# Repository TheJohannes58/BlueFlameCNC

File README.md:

All the Voron build related info and sources I can find and brought into one place for convenance.

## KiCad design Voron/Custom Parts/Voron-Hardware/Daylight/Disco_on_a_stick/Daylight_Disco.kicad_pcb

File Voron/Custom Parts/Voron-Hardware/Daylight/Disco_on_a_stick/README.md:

# Disco on a stick

18 Addressable RGB leds to for a party in your Voron.

## BOM
| Quantity | Value                          | Package |
|----------|--------------------------------|---------|
|       15 | 100nF Capacitor                | 0805    |
|       18 | Addressable RGB LED (WS2812B)  | 5050    |
|        2 | JST-XH (2.54) angled connector | 3pin    |

## Changelog

### V1.1
Added second JST-XH connector to chain to the next Disco on a Stick.  
Thanks to DarkNeutrino for the contribution.

### V1.0
Initial public release.

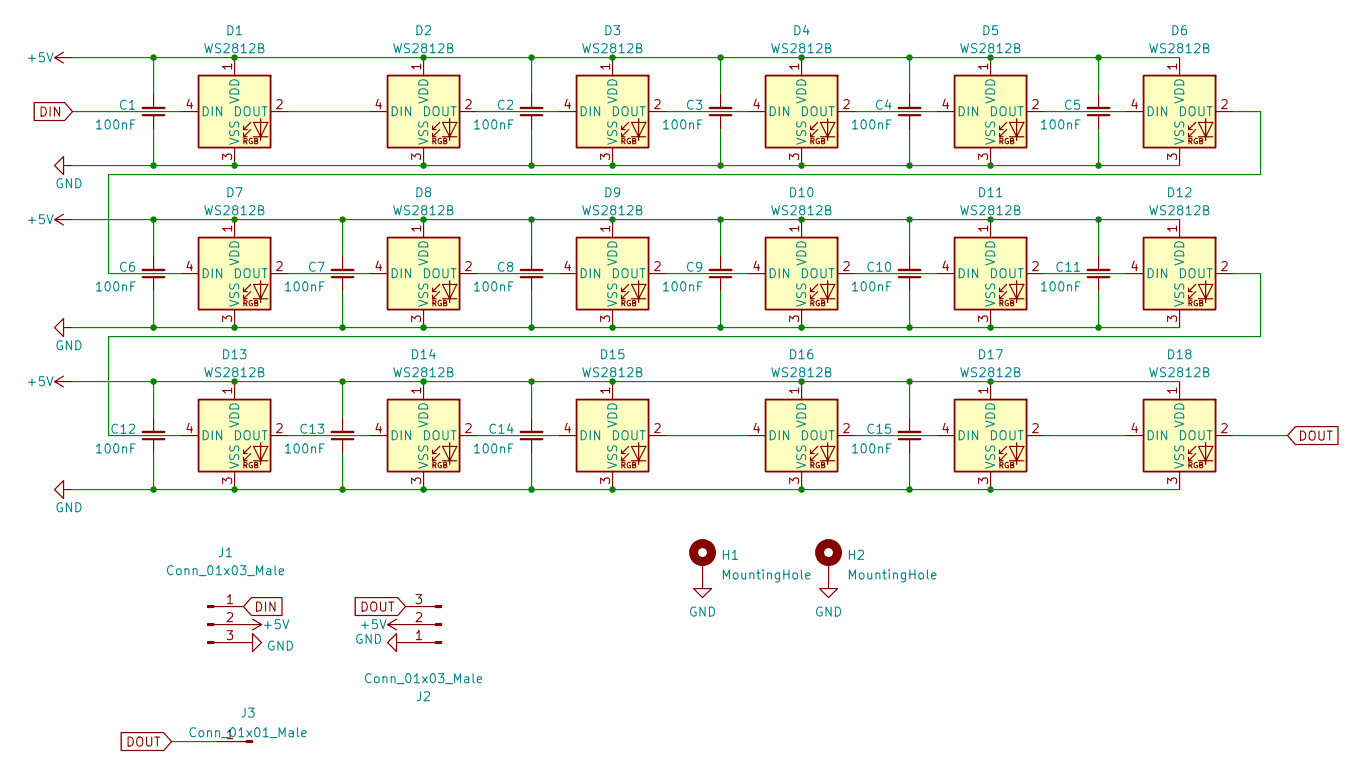
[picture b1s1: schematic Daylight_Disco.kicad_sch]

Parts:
C1, C2, C3, C4, C5, C6, C7, C8, C9, C10, C11, C12, C13, C14, C15: 100nF; C_0805_2012Metric_Pad1.18x1.45mm_HandSolder
D1, D2, D3, D4, D5, D6, D7, D8, D9, D10, D11, D12, D13, D14, D15, D16, D17, D18: WS2812B; LED_WS2812B_PLCC4_5.0x5.0mm_P3.2mm
H1, H2: MountingHole; MountingHole_3.2mm_M3_Pad_Via
J1, J2: Conn_01x03_Male; JST_XH_S3B-XH-A-1_1x03_P2.50mm_Horizontal
J3: Conn_01x01_Male; PinHeader-1-with-SMDpad

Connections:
+5V: C1.2, C2.2, C3.2, C4.2, C5.2, C6.2, C7.2, C8.2, C9.2, C10.2, C11.2, C12.2, C13.2, C14.2, C15.2, D1.1 (VDD), D2.1 (VDD), D3.1 (VDD), D4.1 (VDD), D5.1 (VDD), D6.1 (VDD), D7.1 (VDD), D8.1 (VDD), D9.1 (VDD), D10.1 (VDD), D11.1 (VDD), D12.1 (VDD), D13.1 (VDD), D14.1 (VDD), D15.1 (VDD), D16.1 (VDD), D17.1 (VDD), D18.1 (VDD), J1.2, J2.2
DIN: D1.4 (DIN), J1.1
DOUT: D18.2 (DOUT), J2.3, J3.1
GND: C1.1, C2.1, C3.1, C4.1, C5.1, C6.1, C7.1, C8.1, C9.1, C10.1, C11.1, C12.1, C13.1, C14.1, C15.1, D1.3 (VSS), D2.3 (VSS), D3.3 (VSS), D4.3 (VSS), D5.3 (VSS), D6.3 (VSS), D7.3 (VSS), D8.3 (VSS), D9.3 (VSS), D10.3 (VSS), D11.3 (VSS), D12.3 (VSS), D13.3 (VSS), D14.3 (VSS), D15.3 (VSS), D16.3 (VSS), D17.3 (VSS), D18.3 (VSS), H1.1, H2.1, J1.3, J2.1
unnamed: D1.2 (DOUT), D2.4 (DIN)
unnamed: D2.2 (DOUT), D3.4 (DIN)
unnamed: D3.2 (DOUT), D4.4 (DIN)
unnamed: D4.2 (DOUT), D5.4 (DIN)
unnamed: D5.2 (DOUT), D6.4 (DIN)
unnamed: D6.2 (DOUT), D7.4 (DIN)
unnamed: D7.2 (DOUT), D8.4 (DIN)
unnamed: D8.2 (DOUT), D9.4 (DIN)
unnamed: D10.2 (DOUT), D11.4 (DIN)
unnamed: D9.2 (DOUT), D10.4 (DIN)
unnamed: D11.2 (DOUT), D12.4 (DIN)
unnamed: D12.2 (DOUT), D13.4 (DIN)
unnamed: D13.2 (DOUT), D14.4 (DIN)
unnamed: D14.2 (DOUT), D15.4 (DIN)
unnamed: D15.2 (DOUT), D16.4 (DIN)
unnamed: D16.2 (DOUT), D17.4 (DIN)
unnamed: D17.2 (DOUT), D18.4 (DIN)

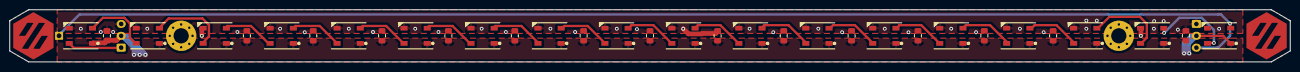
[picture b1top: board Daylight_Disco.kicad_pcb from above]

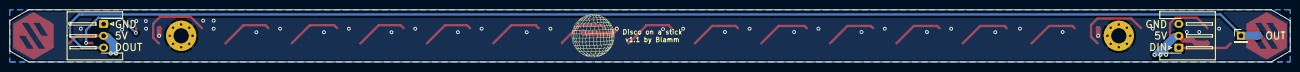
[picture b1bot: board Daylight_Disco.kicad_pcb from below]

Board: 2 copper layers, 270.0 x 11.0 mm, 38 parts (3 on the bottom side), 21 nets.

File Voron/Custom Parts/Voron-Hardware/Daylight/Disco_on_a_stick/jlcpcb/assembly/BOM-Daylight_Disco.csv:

Comment,Designator,Footprint,LCSC
WS2812B,"D1,D10,D11,D12,D13,D14,D15,D16,D17,D18,D2,D3,D4,D5,D6,D7,D8,D9",LED_WS2812B_PLCC4_5.0x5.0mm_P3.2mm,C2761795
100nF,"C1,C10,C11,C12,C13,C14,C15,C2,C3,C4,C5,C6,C7,C8,C9",C_0805_2012Metric_Pad1.18x1.45mm_HandSolder,C28233
Conn_01x01_Male,J3,PinHeader-1-with-SMDpad,
Conn_01x03_Male,J2,JST_XH_S3B-XH-A-1_1x03_P2.50mm_Horizontal,
Conn_01x03_Male,J1,JST_XH_S3B-XH-A-1_1x03_P2.50mm_Horizontal,

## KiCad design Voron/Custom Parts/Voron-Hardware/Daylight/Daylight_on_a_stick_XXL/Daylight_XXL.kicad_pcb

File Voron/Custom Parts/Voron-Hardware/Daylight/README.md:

# Daylight on a stick

The original Daylight on a Stick is a chainable 24V LED bar, to be used with high quality 4000K LEDs to give the illusion of daylight in your Voron. Great when making photo's of your prints, or want to see the colors how they will look in the outside world.  

Ideally popuplated with 90+ CRI LEDs (3V, ~60mA), but currently LCSC does not carry those, so the BOM has 80 CRI ones. Just as bright, bit less accurate color reproduction. Would advice to use the proper ones for the intended experience.  
So if you solder them yourself, get better leds, for example:  
[Digikey CRI90+](https://www.digikey.com/en/products/detail/JB2835AWT-W-U40GA0000-N0000001/2138-JB2835AWT-W-U40GA0000-N0000001CT-ND/10820479)  
[AliExpress CRI95+](https://www.aliexpress.com/item/4000389792048.html) (non affiliate link)

Use any angled 2.54mm(0.1") connector such as a 90 degree pinheader, angled JST-XH or Molex KK254.

The RGB versions use any 4 pin 5050 package addressable led, like the known WS2812B, the SK6812 (with or without white) etcetera. Also 100nF capacitors in 0805 package are added to decouple the leds.

## Varieties

- [Daylight on a Stick](./Daylight_on_a_stick/) (for Voron sizes of 250mm and upwards)
- [Daylight on a Matchstick](./Daylight_on_a_matchstick/) (for V0.1 or other printers for ants)
- [Daylight on a Stick XXL](./Daylight_on_a_stick_XXL/) (for 350 or bigger printers)
- [Disco on a Stick](./Disco_on_a_stick/) (RGB addressable LEDs for the big printers)
- [Rainbow on a Matchstick](./Rainbow_on_a_matchstick/) (RGB addressable LEDS for the small printers)
- [Disco on a Stick XXL](./Disco_on_a_stick_XXL/) (RGB addressable LEDs for for 350 or bigger printers)

## Klipper
Use the regular Daylight on a Stick/Matchstick directly on 24V or hook them up to a spare heater output on your controlboard. In this last case you can control it using:

```
[output_pin daylight]
pin: ##PIN##
pwm: True
cycle_time: 0.01
```

For the RGB ones, put them on the RGB output of your controlboard and configure them according to the [Klipper config reference](https://www.klipper3d.org/Config_Reference.html#neopixel). `chain_length` is 18 for the big stick, 10 for the matchstick.

## Mounting

The [bracket for 2020 profiles](./STL/Brackets_2020.stl) are mounted to the profile using an M3x6 or M3x8 SHCS together with a roll-in nut, and take an M3 heat insert to mount the strip onto the bracket itself.  

On 1515 frames like the V0.1 the [brackets for 1515 profiles](./STL/Brackets_1515_x2.stl) are used. They take an M3 heat insert and clip into the extrusion. Mount the pcb on them with an M3x6 BHCS screw.
The clip geometry used in these was developed by [Zruncho for their ZeroPanels](https://github.com/zruncho3d/ZeroPanels).

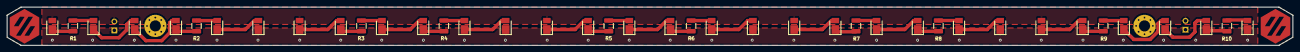
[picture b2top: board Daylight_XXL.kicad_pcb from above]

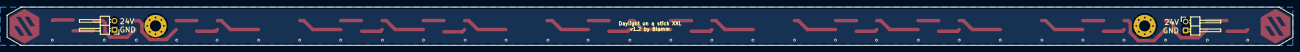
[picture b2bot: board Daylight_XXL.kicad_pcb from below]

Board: 2 copper layers, 370.0 x 11.0 mm, 44 parts (2 on the bottom side), 37 nets.

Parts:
D1, D2, D3, D4, D5, D6, D7, D8, D9, D10, D11, D12, D13, D14, D15, D16, D17, D18, D19, D20, D21, D22, D23, D24, D25, D26, D27, D28, D29, D30: LED_ALT; LED_PLCC_2835_Handsoldering
H1, H2: MountingHole; MountingHole_3.2mm_M3_Pad_Via
J1: Conn_01x02_Female; PinHeader_1x02_P2.54mm_Horizontal_mirrored
J2: Conn_01x02_Female; PinHeader_1x02_P2.54mm_Horizontal
R1, R2, R3, R4, R5, R6, R7, R8, R9, R10: 100R 0.5W; R_1210_3225Metric_Pad1.30x2.65mm_HandSolder

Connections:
+24V: D1.2 (A), D7.2 (A), D13.2 (A), D19.2 (A), D25.2 (A), J1.2, J2.2
GND: D6.1 (K), D12.1 (K), D18.1 (K), D24.1 (K), D30.1 (K), H1.1, H2.1, J1.1, J2.1
unnamed: D1.1 (K), R1.2
unnamed: D2.1 (K), D3.2 (A)
unnamed: D4.1 (K), R2.2
unnamed: D3.1 (K), D4.2 (A)
unnamed: D5.1 (K), D6.2 (A)
unnamed: D5.2 (A), R2.1
unnamed: D7.1 (K), D8.2 (A)
unnamed: D8.1 (K), R3.2
unnamed: D9.2 (A), R3.1
unnamed: D10.1 (K), R4.2
unnamed: D9.1 (K), D10.2 (A)
unnamed: D11.1 (K), D12.2 (A)
unnamed: D11.2 (A), R4.1
unnamed: D13.1 (K), D14.2 (A)
unnamed: D14.1 (K), R5.2
unnamed: D15.1 (K), D16.2 (A)
unnamed: D15.2 (A), R5.1
unnamed: D16.1 (K), R6.2
unnamed: D17.1 (K), D18.2 (A)
unnamed: D19.1 (K), D20.2 (A)
unnamed: D20.1 (K), R7.2
unnamed: D21.1 (K), D22.2 (A)
unnamed: D21.2 (A), R7.1
unnamed: D22.1 (K), R8.2
unnamed: D23.1 (K), D24.2 (A)
unnamed: D23.2 (A), R8.1
unnamed: D25.1 (K), D26.2 (A)
unnamed: D26.1 (K), R9.2
unnamed: D27.1 (K), D28.2 (A)
unnamed: D27.2 (A), R9.1
unnamed: D28.1 (K), D29.2 (A)
unnamed: D29.1 (K), R10.2
unnamed: D30.2 (A), R10.1
unnamed: D2.2 (A), R1.1
unnamed: D17.2 (A), R6.1

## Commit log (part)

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2023-12-23 new file: CAD/Voron_2.4r2_Assembly_STEP.zip new file: Drawing_DXFs/Build_Plate/MIC6_Bed_V2_250.step new file: Drawing_DXFs/Build_Plate/MIC6_Bed_V2_300.step new file: Drawing_DXFs/Build_Plate/MIC6_Bed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
2023-12-23 new file: Voron/Voron-Switchwire/.gitignore new file: Voron/Voron-Switchwire/CAD/Pinion.f3d new file: Voron/Voron-Switchwire/CAD/Pinion.step new file: Voron/Voron-Switchwire/CAD/Switchwire_Assembly_v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
2023-12-23 new file: Voron/Voron-Extras/Klipper_NP++_Language.xml new file: Voron/Voron-Hardware/Afterburner_Toolhead_PCB/CAD/Afterburner-ERCF-PCB.step new file: Voron/Voron-Hardware/Afterburner_Toolhead_PCB/CA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
2023-12-23 new file: Voron/Voron-Parts-DIN/DIN_Mounts/Controllers/Bigtreetech/GTR_2pc.stl new file: Voron/Voron-Parts-DIN/DIN_Mounts/Controllers/Bigtreetech/MOT_EXP.stl new file: Voron/Voron-Parts-DIN/DIN_Mount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
2023-12-23 new file: Voron/Voron-0.2r1/CAD/ADXL_Mounts/MiniSB_adxl_mount_adafruit_19mm_c_c.step new file: Voron/Voron-0.2r1/CAD/ADXL_Mounts/MiniSB_adxl_mount_adafruit_LIS3DH.step new file: Voron/Voron-0.2r1/CAD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
2023-12-23 new file: BIGTREETECH/BIGTREETECH-OCTOPUS-V1.0/3D/BIGTREETECH Octopus V1.0.stp new file: BIGTREETECH/BIGTREETECH-OCTOPUS-V1.0/BIGTREETECH_Octopus_EN_updated_0719.pdf new file: BIGTREETECH/BIGTREETECH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
2023-12-23 new file: PicoPendant/.gitignore new file: PicoPendant/CircuitBoard/PCB_PicoCtl_Pcb_2023-02-23.json new file: PicoPendant/CircuitBoard/README.md new file: PicoPendant/CircuitBoard/SCH_PicoController_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
2023-12-24 new file: OrcaSlicer/.clang-format new file: OrcaSlicer/.dockerignore new file: OrcaSlicer/.doxygen new file: OrcaSlicer/.github/FUNDING.yml new file: OrcaSlicer/.github/ISSUE_TEMPLATE/bug_report.yml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
2023-12-24 new file: bearings/Raindew-F695-RS.png deleted: bearings/Raindew-F695-RS.webp
2023-12-26 new file: bearings/F695-2RS/README.md modified: bearings/images/F695-2RS.png
2023-12-26 new file: bearings/Bearings.md deleted: bearings/F695-2RS.md renamed: bearings/CAD/F695 Bearing.step -> bearings/F695-2RS/CAD/F695 Bearing.step renamed: bearings/CAD/F695-ltk.step -> bearings/F695-2R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
2023-12-26 modified: bearings/625-2RS/images/625-2RS.png new file: bearings/625-2RS/images/ball-bearing-625-2rs.jpg modified: bearings/F695-2RS/images/F695-2RS.png
2023-12-26 new file: bearings/Bearings.md
2023-12-26 deleted: Bearings/Bearings.md renamed: Bearings/625-2RS/README.md -> Build Resources/Bearings/625-2RS/README.md renamed: Bearings/625-2RS/images/625-2RS.png -> Build Resources/Bearings/625-2RS/images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
2023-12-26 modified: Build Resources/Readme.md
2023-12-27 deleted: BIGTREETECH/BIGTREETECH-OCTOPUS-V1.0/3D/BIGTREETECH Octopus V1.0.stp deleted: BIGTREETECH/BIGTREETECH-OCTOPUS-V1.0/BIQU Octopus wiring diagram-V1.0-2021-7-9.png deleted: BIGTREETECH/BIGTREET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
2023-12-27 deleted: BIGTREETECH/BIGTREETECH-OCTOPUS-V1.0/Firmware/DFU Update bootloader/Octopus-DFU Update bootloader - en.pdf deleted: BIGTREETECH/BIGTREETECH-OCTOPUS-V1.0/Firmware/DFU Update bootloader/bootlo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
2023-12-27 new file: Build Resources/Electronics/BIGTREETECH/BIGTREETECH-OCTOPUS-V1.0/BIQU Octopus wiring diagram-V1.0-2021-7-9.png
2023-12-27 new file: Build Resources/Electronics/BIGTREETECH/BIGTREETECH-OCTOPUS-V1.0/Firmware/Marlin-bugfix-2.0.9.3.x/README.md new file: Build Resources/Electronics/BIGTREETECH/BIGTREETECH-OCTOPUS-V1.0/Firmwa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
2023-12-27 new file: Build Resources/Electronics/BIGTREETECH/BIGTREETECH-OCTOPUS-V1.0/BIQU Octopus wiring diagram-V1.0-2021-7-9.png new file: Build Resources/Electronics/BIGTREETECH/BIGTREETECH-OCTOPUS-V1.0/REA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
2023-12-27 new file: Build Resources/Electronics/BIGTREETECH/BIGTREETECH-OCTOPUS-V1.0/Hardware/BIGTREETECH Octopus - PIN.pdf new file: Build Resources/Electronics/BIGTREETECH/BIGTREETECH-OCTOPUS-V1.0/Hardware/B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
2023-12-27 new file: Build Resources/Electronics/BIGTREETECH/BIGTREETECH-OCTOPUS-V1.0/Firmware/DFU Update bootloader/Octopus-DFU Update bootloader - en.pdf new file: Build Resources/Electronics/BIGTREETECH/BIGT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
2023-12-27 new file: temp/RepRapFirmware/F446-OctoPus/README.md new file: temp/RepRapFirmware/F446-OctoPus/filaments/nop.g new file: temp/RepRapFirmware/F446-OctoPus/firmware.bin new file: temp/RepRapFirmware/F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
2023-12-27 renamed: Build Resources/temp/Marlin-bugfix-2.0.9.3.x/.editorconfig -> Build Resources/Electronics/temp/Marlin-bugfix-2.0.9.3.x/.editorconfig renamed: Build Resources/temp/Marlin-bugfix-2.0.9.3.x/.gi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
2023-12-27 renamed: Build Resources/Electronics/BIGTREETECH/temp/RepRapFirmware/F446-OctoPus/README.md -> Build Resources/Electronics/BIGTREETECH/BIGTREETECH-OCTOPUS-V1.0/Firmware/RepRapFirmware/F446-OctoPus/RE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
2023-12-27 renamed: Build Resources/Electronics/BIGTREETECH/temp/RepRapFirmware/RRFBuild-SourceCode/.vscode/.cortex-debug.peripherals.state.json -> Build Resources/Electronics/BIGTREETECH/BIGTREETECH-OCTOPUS-V1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
2023-12-27 renamed: Build Resources/Electronics/BIGTREETECH/temp/RepRapFirmware/RRFBuild-SourceCode/DuetWiFiSocketServer/.cproject -> Build Resources/Electronics/BIGTREETECH/BIGTREETECH-OCTOPUS-V1.0/Firmware/Re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
2023-12-27 renamed: Build Resources/Electronics/BIGTREETECH/temp/RepRapFirmware/RRFBuild-SourceCode/CoreN2G/src/AnalogIn.h -> Build Resources/Electronics/BIGTREETECH/BIGTREETECH-OCTOPUS-V1.0/Firmware/RepRapFirm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
2023-12-27 renamed: Build Resources/Electronics/BIGTREETECH/BIGTREETECH-OCTOPUS-V1.0/3D/BIGTREETECH Octopus V1.0.stp -> BIGTREETECH/BIGTREETECH-OCTOPUS-V1.0-master/3D/BIGTREETECH Octopus V1.0.stp renamed: Build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
2023-12-27 deleted: "BIGTREETECH/BIGTREETECH-OCTOPUS-V1.0-master/Firmware/DFU Update bootloader/Octopus-DFU\346\233\264\346\226\260\345\274\225\345\257\274\347\250\213\345\272\217-\344\270\255\346\226\207.pdf"
2023-12-27 modified: .vscode/settings.json modified: Build Resources/Listings/Buylist.md
2023-12-29 new file: Build Resources/Frames/Fermio/Readme.md new file: Build Resources/Frames/Misumi/2019_US_2724.pdf new file: Build Resources/Frames/Misumi/HFSB6-3060-520-AH105-BH415-AV180.pdf new file: Build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
2023-12-29 modified: Build Resources/Frames/Readme.md new file: Build Resources/Frames/images/misumi alu prof.png
2023-12-29 Rename misumi alu prof.png to misumi_alu-prof.png
2023-12-29 new file: Build Resources/Frames/Misumi/Readme.md new file: Build Resources/Frames/images/30x60-Aluminum-Extrusion-6_Series_Base_30.png
2023-12-29 new file: Build Resources/Fasteners/Voron Switchwire/Readme.md new file: Build Resources/Fasteners/images/VRN-SW-HRDWR-KIT.jpg
2023-12-29 modified: Build Resources/Fasteners/Voron Switchwire/Readme.md new file: Build Resources/Fasteners/images/VRN-SW-TNUTS.png
2023-12-30 modified: Build Resources/Fasteners/Voron 2.4/Readme.md new file: Build Resources/Fasteners/images/MCH-NT-HH-M3-50.jpg new file: Build Resources/Fasteners/images/VRN-V24-TNUTS.jpg
2023-12-30 modified: Build Resources/Fasteners/Voron Switchwire/Lecktor.com.md
2023-12-30 new file: Build Resources/Frames/next.csv
2023-12-30 modified: Build Resources/Frames/next.csv deleted: Build Resources/Frames/next.csv
2023-12-30 modified: Build Resources/Frames/template.csv deleted: Build Resources/Listings/BuylistTemplate.md renamed: Build Resources/Bearings/625-2RS/README.md -> Build Resources/Motion/Bearings/625-2RS/READM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
2023-12-30 modified: Build Resources/Buildplate/readme.md new file: Build Resources/Electronics/Stepper Motors/Readme.md new file: Build Resources/Electronics/images/17HS15-1504S1.jpg new file: Build Resources/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
2023-12-30 modified: Build Resources/Electronics/Stepper Motors/17HS15-1504S1 stepper.md modified: Build Resources/Electronics/Stepper Motors/17HS15-1504S1 stepper.md
2023-12-30 modified: Build Resources/Electronics/Power Supply/LRS-350-24.md
2023-12-30 new file: Build Resources/Electronics/Stepper Motors/17HS08-1004S-H.md new file: Build Resources/Electronics/images/17HS08-1004S-H.jpg new file: Build Resources/Electronics/images/17HS08-1004S-H.webp
2023-12-30 modified: Build Resources/Electronics/Stepper Motors/Readme.md renamed: Build Resources/Electronics/images/17HS15-1504S1 - Copy.webp -> Build Resources/Electronics/images/17HS15-1504S1 - shift.webp
2023-12-30 new file: Build Resources/Electronics/Stepper Motors/PDF/17HS08-1004S-H.pdf new file: Build Resources/Electronics/Stepper Motors/PDF/17HS15-1504S1.pdf new file: Build Resources/Electronics/Stepper Mo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
2023-12-30 modified: Build Resources/Electronics/Power Supply/LRS-350-24.md new file: Build Resources/Electronics/Power Supply/PDF/LRS-350-24.pdf new file: Build Resources/Electronics/Power Supply/PDF/RS-25.pdf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
2023-12-31 modified: Build Resources/Electronics/Readme.md modified: Build Resources/Fasteners/Readme.md
2023-12-31 modified: Build Resources/Fasteners/Readme.md deleted: Build Resources/Fasteners/images/MCH-NT-HH-M3-50.jpg deleted: Build Resources/Fasteners/images/VRN-24-HRDWR-KIT-BLK.jpg new file: Build Resource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
2023-12-31 new file: Build Resources/Fasteners/Voron Switchwire/Bolt-Depot.md new file: Build Resources/Fasteners/Voron Switchwire/McMaster.md
2023-12-31 modified: Build Resources/Fasteners/Voron Switchwire/Switchwire.csv new file: Build Resources/Fasteners/Voron Switchwire/Switchwire.xlsx
2024-01-01 new file: Build Resources/Electronics/Power Supply/LRS-150-24.md new file: Build Resources/Electronics/Power Supply/PDF/LRS-150.PDF new file: Build Resources/Electronics/images/LRS-150-24.webp
2024-01-01 Rename LRS-150.PDF to LRS-150.pdf
2024-01-01 modified: Build Resources/Electronics/Power Supply/LRS-150-24.md modified: Build Resources/Electronics/Power Supply/LRS-350-24.md modified: Build Resources/Electronics/Power Supply/RS-25-5.md
2024-01-01 deleted: Build Resources/Electronics/Power Supply/CAD/LRS-150-24.stl deleted: Build Resources/Electronics/Power Supply/CAD/LRS-350-24.stl deleted: Build Resources/Electronics/Power Supply/CAD/RS-25-5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
2024-01-01 new file: Build Resources/Electronics/Fans/CAD/414FH.stp new file: Build Resources/Electronics/Fans/readme.md new file: Build Resources/Electronics/images/FYSETC.webp new file: Build Resources/Electr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
2024-01-01 modified: Build Resources/Electronics/images/FYSETC.webp
2024-01-01 new file: Build Resources/Electronics/Wiring/readme.md
2024-01-02 modified: Build Resources/Electronics/Fans/readme.md modified: Build Resources/Electronics/Wiring/readme.md deleted: Build Resources/Electronics/images/FYSETC.webp new file: Build Resources/Electroni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
2024-01-02 modified: Build Resources/Electronics/images/43030-0007.webp modified: Build Resources/Electronics/images/43031-0007.webp modified: Build Resources/Electronics/images/43640-0201.webp modified: Build 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
2024-01-02 modified: Build Resources/Electronics/Fans/readme.md modified: Build Resources/Electronics/Wiring/readme.md new file: Build Resources/Electronics/images/19164-0017.jpg new file: Build Resources/Elect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
2024-01-03 deleted: Build Resources/Electronics/images/2Pcs-GDSTIME-60MM-Axial-Fan-DC-12V-24V-60x60x20MM-Dual-Ball-Cooler-6CM-PC-Computer-Case.jpg_640x640.jpg_.webp new file: Build Resources/Electronics/images/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
2024-01-03 new file: Build Resources/Electronics/images/Keenovo-2.webp new file: Build Resources/Electronics/images/Keenovo-3.webp new file: Build Resources/Electronics/images/Keenovo-4.JPG new file: Build Reso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
2024-01-03 modified: Build Resources/Buildplate/readme.md new file: Build Resources/images/buildplate-layers.webp
2024-01-04 new file: Voron/Readme,md
2024-01-04 renamed: Voron/Readme,md -> Voron/Readme.md
2024-01-05 new file: Voron/images/iso-v.webp
2024-01-06 renamed: Voron/Voron-Extras/Bed_Models/SuperSlicer/Legacy/VL_bed_model.stl -> Voron/Custom Parts/Voron-Extras/Bed_Models/SuperSlicer/Legacy/VL_bed_model.stl renamed: Voron/Voron-Extras/Bed_Models/Sup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
2024-01-07 new file: BIGTREETECH/BIGTREETECH-OCTOPUS-V1.0-master/3D/BIGTREETECH Octopus V1.0.stp new file: BIGTREETECH/BIGTREETECH-OCTOPUS-V1.0-master/BIGTREETECH_Octopus_EN_updated_0719.pdf new file: BIGTREETE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
2024-01-07 deleted: Voron/TOC-bu.md
2024-01-07 modified: Voron/Printers/Voron-Trident/README.md
2024-01-07 deleted: Voron/Printers/Voron-Trident/.github/workflows/ci-build.yml
2024-01-07 modified: Voron/Readme.md deleted: Voron/TOC.md
2024-01-07 new file: Voron/PDF/Afterburner.pdf new file: Voron/PDF/Assembly_Manual_2.4r2.pdf new file: Voron/PDF/Assembly_Manual_SB.pdf new file: Voron/PDF/Assembly_Manual_SB_High_Contrast_7-7-23.pdf new file: 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
2024-01-09 modified: Build Resources/Electronics/images/KB-INLET-10A.webp
2024-01-10 modified: Build Resources/Electronics/images/43031-0007.webp modified: Build Resources/Electronics/images/43640-0201.webp modified: Build Resources/Electronics/images/SXH-001T-P0.6N.webp new file: Bu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
2024-01-10 modified: Build Resources/Electronics/images/XHP-4.webp
2024-01-10 modified: Blue Flame/Electrical/Stepper Motors/Nema 23/23HS30-2804S.md
2024-01-10 modified: Blue Flame/Electrical/Stepper Motors/Nema 23/23HS30-2804S.md modified: Blue Flame/Electrical/Stepper Motors/Nema 23/23HS30-3004S.md
2024-01-11 modified: Blue Flame/Electrical/Stepper Motors/Readme.md
